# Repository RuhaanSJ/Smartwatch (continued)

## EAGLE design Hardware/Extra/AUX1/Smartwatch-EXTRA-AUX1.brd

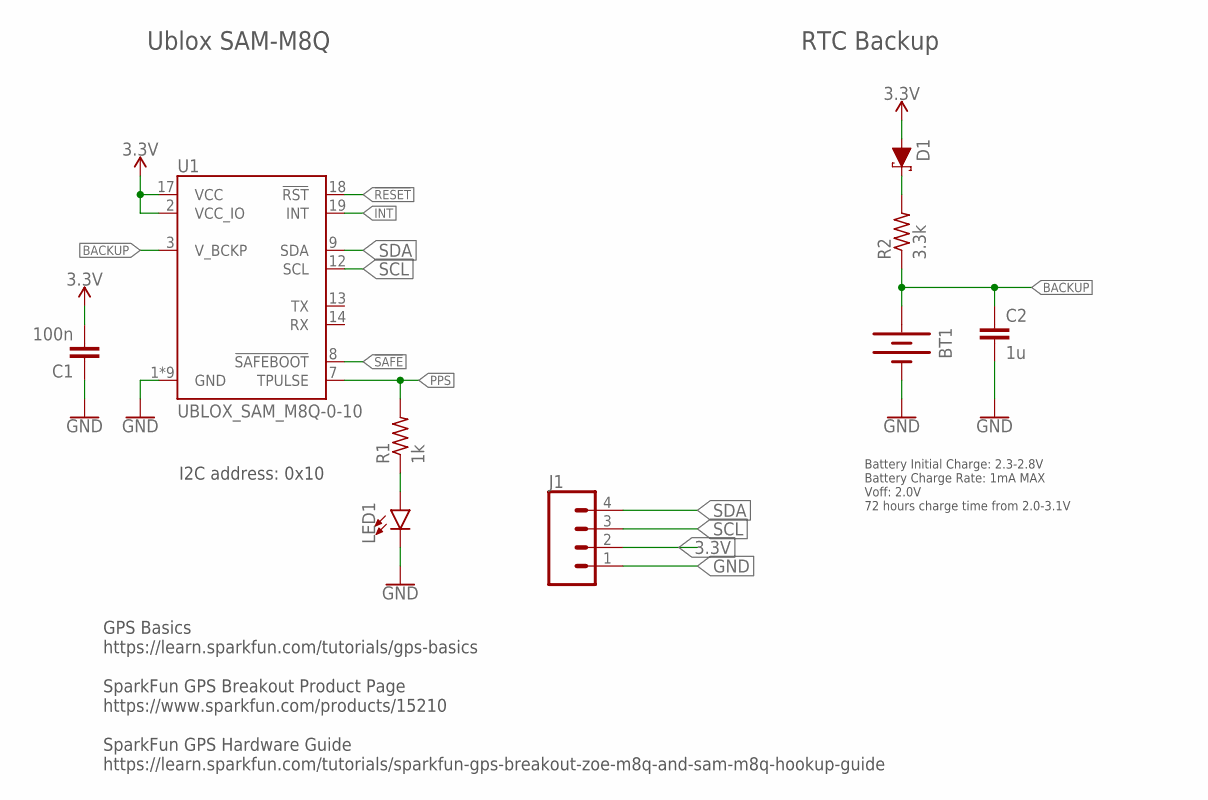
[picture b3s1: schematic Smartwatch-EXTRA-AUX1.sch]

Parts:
BT1: ML414H_IV01E_BATTERY; ML414H_IV01E
C1: 100n; C0603
C2: 1u; C0603
D1: SCHOTTKY-USC; USC
J1: CONN_041.27MM; 1X04_1.27MM
LED1: LED0603; LED-0603
R1: 1k; R0603
R2: 3.3k; R0603
U1: UBLOX_SAM_M8Q-0-10; SAM-M8Q

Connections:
3.3V: C1.2, D1.+ (A), J1.2, U1.2 (VCC_IO), U1.17 (VCC)
!RESET: U1.18 (!RST)
!SAFE: U1.8 (!SAFEBOOT)
BACKUP: BT1.+, C2.1, R2.1, U1.3 (V_BCKP)
GND: BT1.-, C1.1, C2.2, J1.1, LED1.C, U1.1 (GND), U1.4 (GND), U1.5 (GND), U1.6 (GND), U1.10 (GND), U1.11 (GND), U1.15 (GND), U1.16 (GND), U1.20 (GND)
INT: U1.19 (INT)
unnamed: D1.- (C), R2.2
unnamed: LED1.A, R1.1
PPS: R1.2, U1.7 (TPULSE)
SCL: J1.3, U1.12 (SCL)
SDA: J1.4, U1.9 (SDA)

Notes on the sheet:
I2C address: 0x10
Ublox SAM-M8Q
RTC Backup
Battery Initial Charge: 2.3-2.8V Battery Charge Rate: 1mA MAX Voff: 2.0V 72 hours charge time from 2.0-3.1V
GPS Basics https://learn.sparkfun.com/tutorials/gps-basics SparkFun GPS Breakout Product Page https://www.sparkfun.com/products/15210 SparkFun GPS Hardware Guide https://learn.sparkfun.com/tutorials/sparkfun-gps-breakout-zoe-m8q-and-sam-m8q-hookup-guide

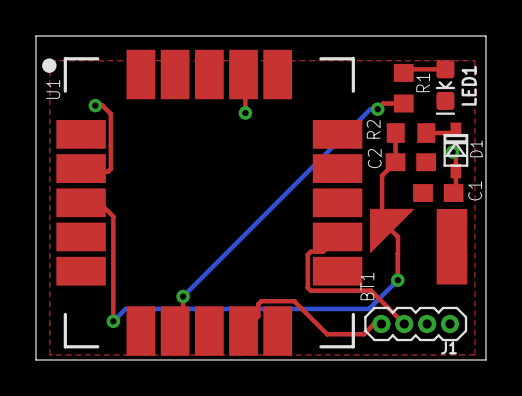
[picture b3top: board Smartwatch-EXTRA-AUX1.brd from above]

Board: 2 copper layers, 25.0 x 18.0 mm, 9 parts (0 on the bottom side), 8 nets.

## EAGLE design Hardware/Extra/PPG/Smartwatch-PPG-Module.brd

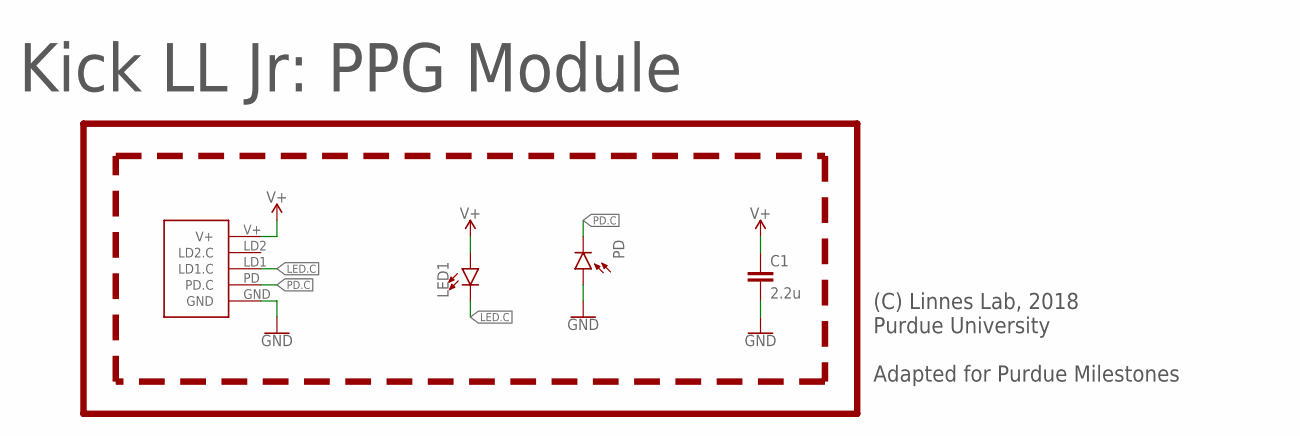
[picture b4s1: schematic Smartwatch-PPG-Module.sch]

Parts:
C1: 2.2u; C0603
J1: PPG.MODULE.2
LED1: LED0805; LED-0805
PD: PHOTODIODE.-SMD.GULLWING; 2-SMD.GULLWING
U$3: LINNES.LAB.LOGO

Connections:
GND: C1.2, J1.GND, PD.+ (A)
LED.C: J1.LD1 (LD1.C), LED1.C
PD.C: J1.PD (PD.C), PD.- (C)
V+: C1.1, J1.V+, LED1.A

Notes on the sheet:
Kick LL Jr: PPG Module
(C) Linnes Lab, 2018 Purdue University Adapted for Purdue Milestones

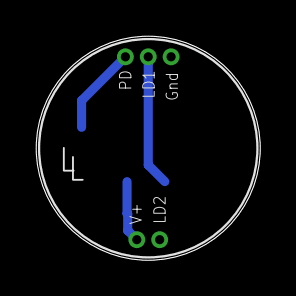
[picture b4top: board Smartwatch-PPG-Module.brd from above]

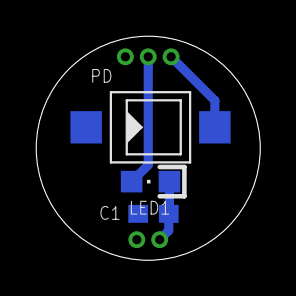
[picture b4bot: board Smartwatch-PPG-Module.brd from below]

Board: 2 copper layers, 12.4 x 12.4 mm, 5 parts (3 on the bottom side), 4 nets.

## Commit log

2021-02-07 Firware commit
2021-02-07 Firmware
2021-02-07 Hardware
2021-02-07 Hardware/Basic/Bottom/Smartwatch-BASIC-BOTTOM_BOM.xlsx
2021-02-07 Mechanical
2021-02-13 This group contains elements or signals that cannot be deleted,as the operation cannot be back-annotated
2021-02-13 USB, OLED Microcontroller and SD added. Need to add RTC
2021-02-13 USB, OLED Microcontroller, SD and RTC added
2021-02-15 Added FTDI
2021-02-17 Bottom board routed
2021-02-20 Top board routing started
2021-02-21 Top Board Routed
2021-02-27 Rearranging Top Board
2021-02-27 Rearranged Top Board
2021-03-06 Fixing top board issues
2021-03-06 Top Board Complete
2021-03-06 Bottom Board Complete
2021-03-06 Organized Schematics and Silkscreens for both boards
2021-03-07 Started Firmware Developement
2021-03-07 Fixed Top Board Issue
2021-03-07 Fixed Bottom Board Issue
2021-03-07 Started wokring on Extra features
2021-03-13 PPG library added
2021-03-14 Fixed Top Board Polygon
2021-03-18 Fixed Bottom Board Mistakes
2021-03-18 Top board fixed some traces
2021-03-20 Top Board- Minor problems correct
2021-03-20 PPG Board Added
2021-03-20 Header Pins Fixed
2021-03-20 Top Board airwire fixed
2021-03-20 Top Board BOM WIP
2021-03-22 Extra features updated
2021-03-24 Extra Silkscreens updated
2021-03-27 Encoder Added, Silkscreen Updated, Bom Updated
2021-03-27 Microphone Removed,Silkscreen Updated, Bom Updated
2021-03-27 Board Resized and Repositioned
2021-03-27 BOMs finished
2021-04-01 Encoder changed, BOMs updated
2021-04-03 Removed GPS, rearranged some other components
2021-04-03 GPS Removed, added back original display, kept pads for adafruit display
2021-04-10 Silkscreens fixed, Airwires removed
